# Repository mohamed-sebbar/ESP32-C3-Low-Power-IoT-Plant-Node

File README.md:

# ESP32-C3 Low-Power IoT Plant Node Rev 2.0

> Design and implementation of a compact low-power ESP32-C3 hardware platform for smart plant monitoring, environmental sensing and automated irrigation.

---

---

## Overview

This repository presents the complete hardware design of a compact ESP32-C3 based IoT plant monitoring node developed as an engineering-focused redesign of a previously demonstrated smart irrigation concept.

Where the original project validated the overall application concept, this work focuses on the complete hardware architecture, RF-aware PCB layout, mixed-signal design, manufacturability, power integrity, and long-term maintainability of a production-oriented embedded platform.

The platform integrates environmental sensing, wireless communication, battery-ready power management and irrigation control within a compact four-layer PCB specifically designed for constrained enclosure geometries.

The goal of this repository is to document the engineering process behind the hardware rather than only presenting a finished PCB.

---

## Contents

- [Overview](#overview)
- [Key Features](#key-features)
- [Hardware Gallery](#hardware-gallery)
- [Repository Structure](#repository-structure)
- [Hardware Architecture](#hardware-architecture)
- [PCB Design Highlights](#pcb-design-highlights)
- [RF Design](#rf-design)
- [Manufacturing](#manufacturing)
- [Documentation](#documentation)
- [Future Work](#future-work)
- [Acknowledgements](#acknowledgements)
- [License](#license)
- [Author](#author)
- [Contact](#contact)

---

## Key Features

- Custom 4-layer PCB
- ESP32-C3 Wi-Fi MCU
- External SPI Flash
- USB-C Programming & Power
- Battery-ready architecture
- Battery charging circuitry
- Reverse polarity protection
- SHT40 Temperature & Humidity Sensor
- Capacitive Soil Moisture Interface
- MOSFET-controlled irrigation pump
- 2.4 GHz PCB antenna based on TI reference design
- RF-aware PCB layout
- Mixed-signal architecture
- Ground stitching
- Manufacturing-ready design

---

## Hardware Gallery

---

## Repository Structure

```text
ESP32-C3-Low-Power-IoT-Plant-Node

├── Hardware/
│   ├── KiCad Project
│   ├── Production
│   └── Libraries
│
├── Docs/
│   ├── 01_Schematic.pdf
│   └── 02_PCB_Assembly.pdf
│
├── LTspice_Sim
│
├── Images/
│
├── Logos/
│
├── 3D Models/
│
├── LICENSE
└── README.md
```
### Quick Access

- 📁 [Hardware](Hardware/)
- 📁 [Docs](Docs/)
- 📁 [LTspice_Sim](LTspice_Sim/)
- 📁 [Images](Images/)
- 📁 [Logos](Logos/)
- 📁 [3D Models](3D%20Models/)

---

## Hardware Architecture

The platform combines multiple engineering domains within a compact embedded hardware design.

**Processing**

- ESP32-C3
- External SPI Flash

**Environmental Sensing**

- SHT40 Temperature & Humidity
- Capacitive Soil Moisture Sensor

**Irrigation**

- MOSFET Pump Driver
- External Pump Connector

**Connectivity**

- Wi-Fi
- USB-C

**Power**

- USB & Battery powered
- Battery charging supported
- Reverse polarity protection
- Battery voltage monitoring

---

## PCB Design Highlights

The PCB was designed from the ground up with emphasis on engineering practices commonly employed in professional embedded hardware development.

Highlights include

- Four-layer stack-up
- Continuous ground reference planes
- Controlled RF keep-out
- Ground stitching vias
- Short crystal routing
- Careful decoupling placement
- USB differential routing
- Mixed analog/digital partitioning
- Compact constrained mechanical form factor

---

## RF Design

The wireless subsystem employs a PCB antenna derived from Texas Instruments reference **AN043** recommendations.

The antenna region includes

- dedicated RF keep-out
- controlled ground clearance
- dedicated feed routing
- configurable matching network

The initial values of the antenna matching network (L2, C21, C22) were selected based on theoretical calculations and RF design recommendations. Although these values are expected to operate correctly, final impedance matching should be verified after fabrication. For this reason, it is recommended to initially designate L2, C21, and C22 as DNP (Do Not Populate) and populate them only after RF characterization and tuning of the assembled hardware.

Detailed RF design notes will be provided in future documentation.

---

## Manufacturing

The repository includes fabrication outputs required for PCB production.

Included

- Gerber files
- Drill files
- Fabrication outputs

A generic Bill of Materials (BOM) is provided for design reference. Manufacturer-specific part numbers and sourcing information are intentionally omitted, allowing designers the flexibility to select equivalent components based on availability, cost, or project-specific requirements.

---

## Documentation

The repository documentation is being expanded and currently includes

- Schematic
- PCB Assembly
- LTspice power rail stability and transient response plots

Planned additions

- PCB Design Report
- RF Design Notes
- Signal and Power Integrity Discussion
- Design Validation

---

## Future Work

- Firmware adaptation
- Antenna impedance tuning
- Battery validation [Done]
- Power consumption characterization [Done]
- Environmental testing
- Long-term field deployment
- Companion mobile application integration

---

## Acknowledgements

The 3D planter model used in the project renders was created by **Lewis**. Full credit goes to the original author. The original model is available on the **Thingiverse** [Profile](https://www.thingiverse.com/thing:3537287).

The plant icon used on the PCB silkscreen is **"Smart Plant"** by **Anton Handal Saputra**, sourced from the **Noun Project**, and is used under the **Creative Commons Attribution 3.0 (CC BY 3.0)** license: https://thenounproject.com/browse/icons/term/smart-plant/

---

## License

The hardware design files are released under the CERN Open Hardware Licence Version 2 – Permissive (CERN-OHL-P). The accompanying files and written documentation remain © 2026 SEBBAR Mohamed and are provided for reference purposes only.

See [LICENSE](LICENSE) for details.

---

## Author

**Mohamed Sebbar**

Master's Degree in Computer Engineering and Embedded Systems

Faculty of Sciences, Agadir, Morocco

---

## Contact

If you have questions about this project, or would like to discuss the design feel free to:

- Open an [Issue](../../issues).
- Connect with me on [LinkedIn](https://www.linkedin.com/in/mohamedsebbar/).
- Or contact me via [email](mailto:sebbar.mohamed66@gmail.com).

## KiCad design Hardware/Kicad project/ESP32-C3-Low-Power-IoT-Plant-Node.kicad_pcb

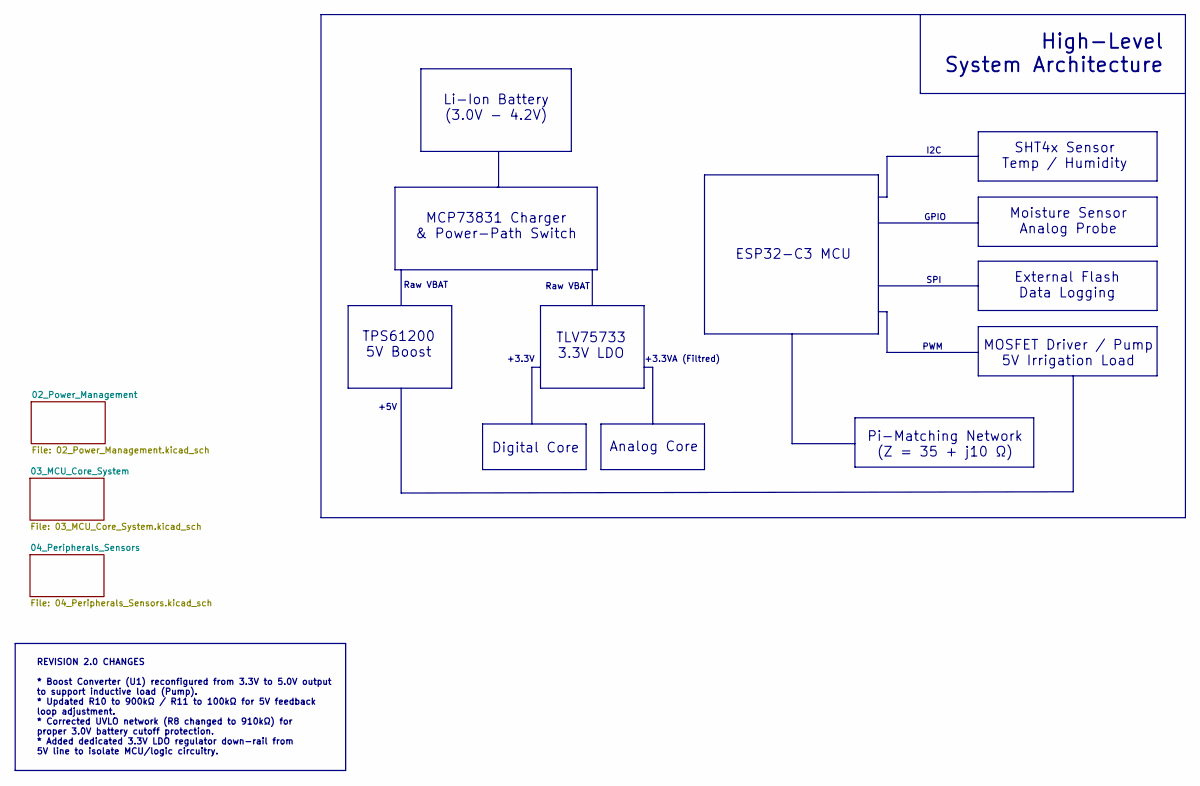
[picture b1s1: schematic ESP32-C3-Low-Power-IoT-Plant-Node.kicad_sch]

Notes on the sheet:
Moisture Sensor Analog Probe
Analog Core
ESP32-C3 MCU
Raw VBAT
+3.3VA (Filtred)
I2C
+5V
GPIO
Pi-Matching Network (Z = 35 + j10 Ω)
High-Level System Architecture
TLV75733 3.3V LDO
SPI
Digital Core
TPS61200 5V Boost
MOSFET Driver / Pump 5V Irrigation Load
REVISION 2.0 CHANGES * Boost Converter (U1) reconfigured from 3.3V to 5.0V output to support inductive load (Pump). * Updated R10 to 900kΩ / R11 to 100kΩ for 5V feedback loop adjustment. * Corrected UVLO network (R8 changed to 910kΩ) for proper 3.0V battery cutoff protection. * Added dedicated 3.3V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
SHT4x Sensor Temp / Humidity
PWM
MCP73831 Charger & Power-Path Switch
+3.3V
Li-Ion Battery (3.0V - 4.2V)
External Flash Data Logging

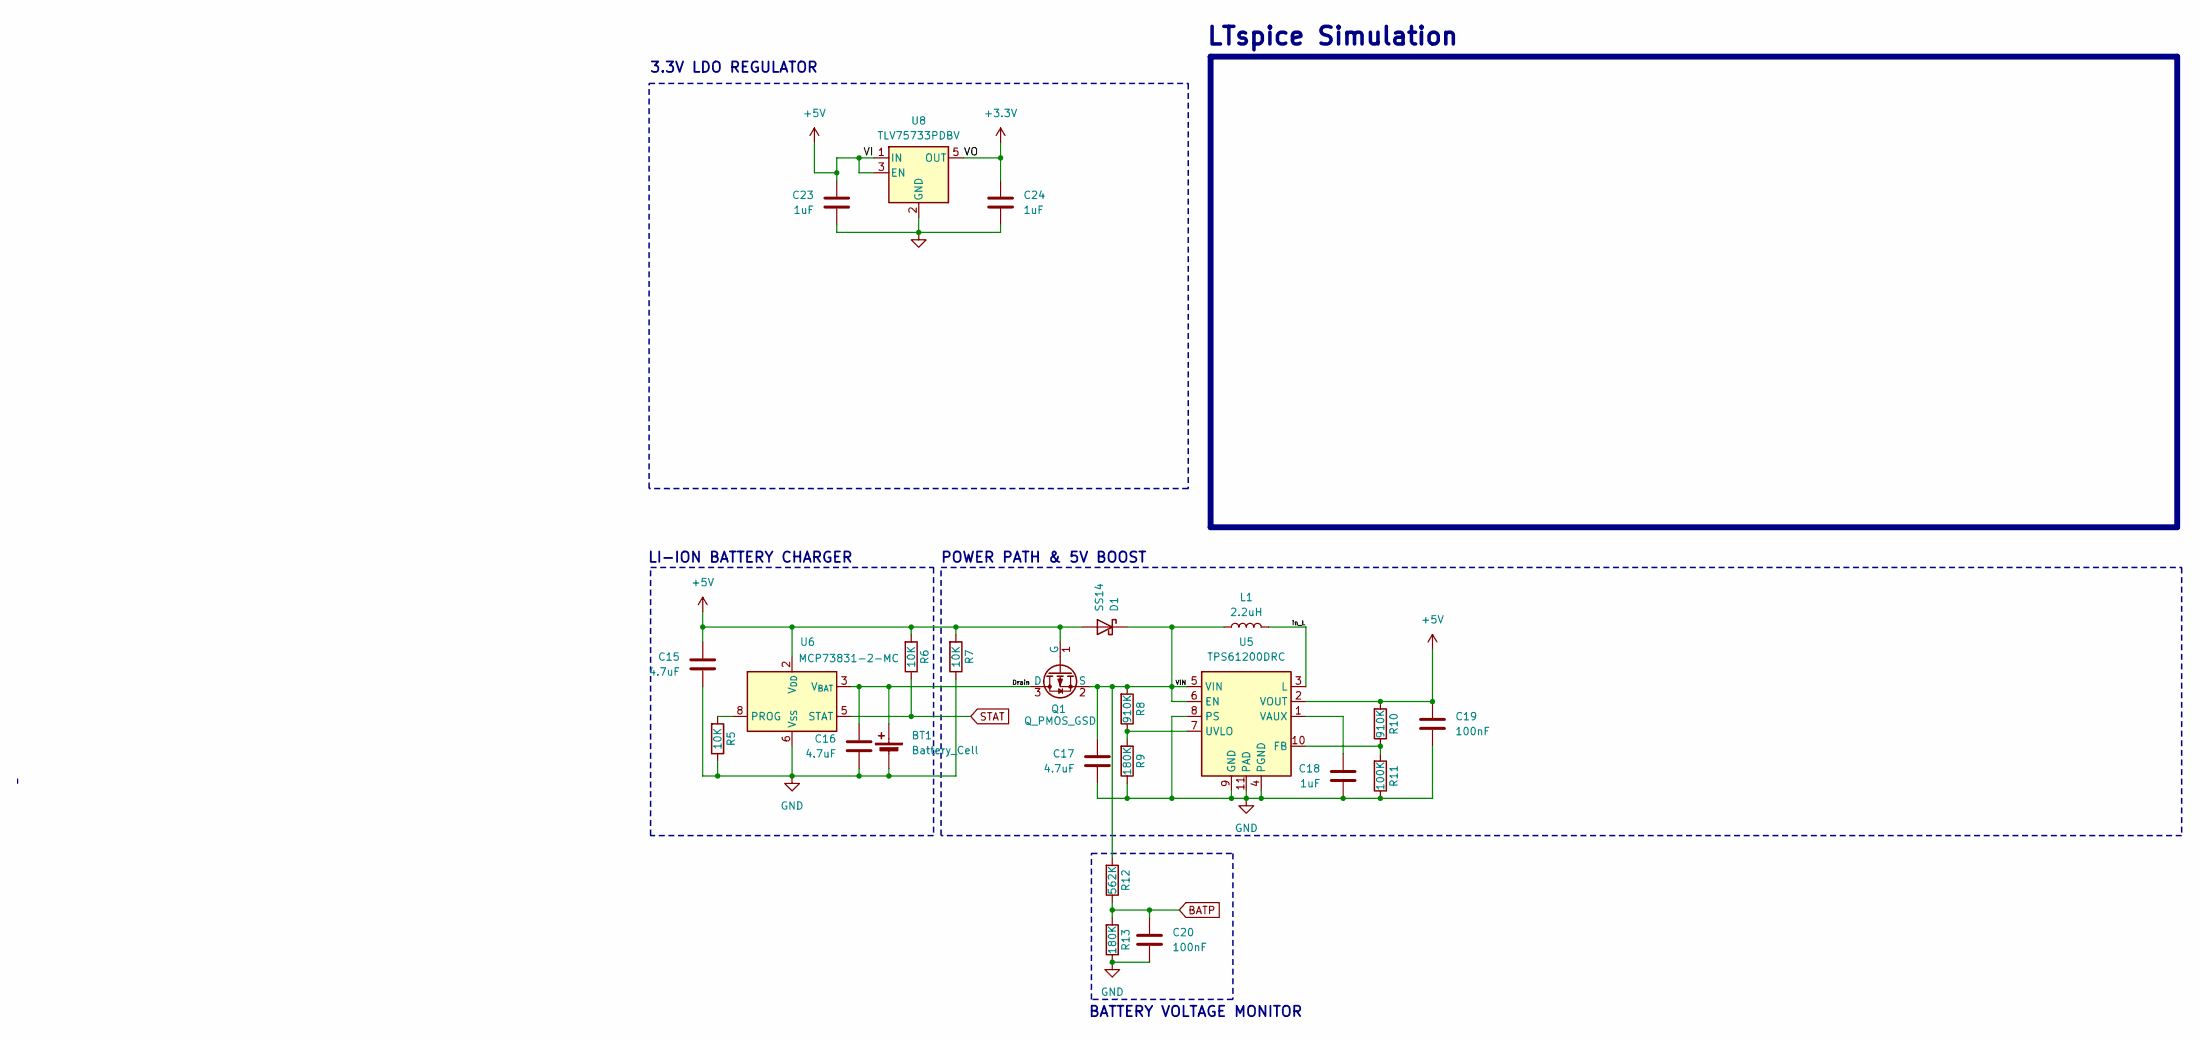
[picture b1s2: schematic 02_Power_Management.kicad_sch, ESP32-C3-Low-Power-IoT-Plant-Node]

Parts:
BT1: Battery_Cell; JST_PH_S2B-PH-K_1x02_P2.00mm_Horizontal
C15, C16, C17: 4.7uF; C_0402_1005Metric
C18, C23, C24: 1uF; C_0402_1005Metric
C19, C20: 100nF; C_0402_1005Metric
D1: SS14; D_SMA
L1: 2.2uH; R_0402_1005Metric
Q1: Q_PMOS_GSD; SOT-23
R5, R6, R7: 10K; R_0402_1005Metric
R8, R10: 910K; R_0402_1005Metric
R9, R13: 180K; R_0402_1005Metric
R11: 100K; R_0402_1005Metric
R12: 562K; R_0402_1005Metric
U5: TPS61200DRC; Texas_S-PVSON-N10_ThermalVias
U6: MCP73831-2-MC; DFN-8-1EP_3x2mm_P0.5mm_EP1.75x1.45mm
U8: TLV75733PDBV; SOT-23-5

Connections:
+3.3V: C24.1, U8.5 (OUT); also elsewhere on the board
+5V: C15.1, C19.1, C23.1, D1.2 (A), Q1.1 (G), R6.2, R7.2, R10.2, U5.2 (VOUT), U6.1 (V_{DD}), U6.2 (V_{DD}), U8.1 (IN), U8.3 (EN); also elsewhere on the board
/02_Power_Management/Drain: BT1.1 (+), C16.1, Q1.3 (D), U6.3 (V_{BAT}), U6.4 (V_{BAT})
/02_Power_Management/VIN: C17.1, D1.1 (K), L1.1, Q1.2 (S), R8.2, R12.2, U5.5 (VIN), U5.6 (EN)
/02_Power_Management/in_L: L1.2, U5.3 (L)
BATP: C20.1, R12.1, R13.2; also elsewhere on the board
GND: BT1.2 (-), C15.2, C16.2, C17.2, C18.2, C19.2, C20.2, C23.2, C24.2, R5.1, R7.1, R9.1, R11.1, R13.1, U5.4 (PGND), U5.8 (PS), U5.9 (GND), U5.11 (PAD), U6.6 (V_{SS}), U8.2 (GND); also elsewhere on the board
unnamed: R10.1, R11.2, U5.10 (FB)
unnamed: R8.1, R9.2, U5.7 (UVLO)
unnamed: C18.1, U5.1 (VAUX)
unnamed: R5.2, U6.8 (PROG)
STAT: R6.1, U6.5 (STAT); also elsewhere on the board

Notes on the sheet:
BATTERY VOLTAGE MONITOR
POWER PATH & 5V BOOST
3.3V LDO REGULATOR
LTspice Simulation
LI-ION BATTERY CHARGER

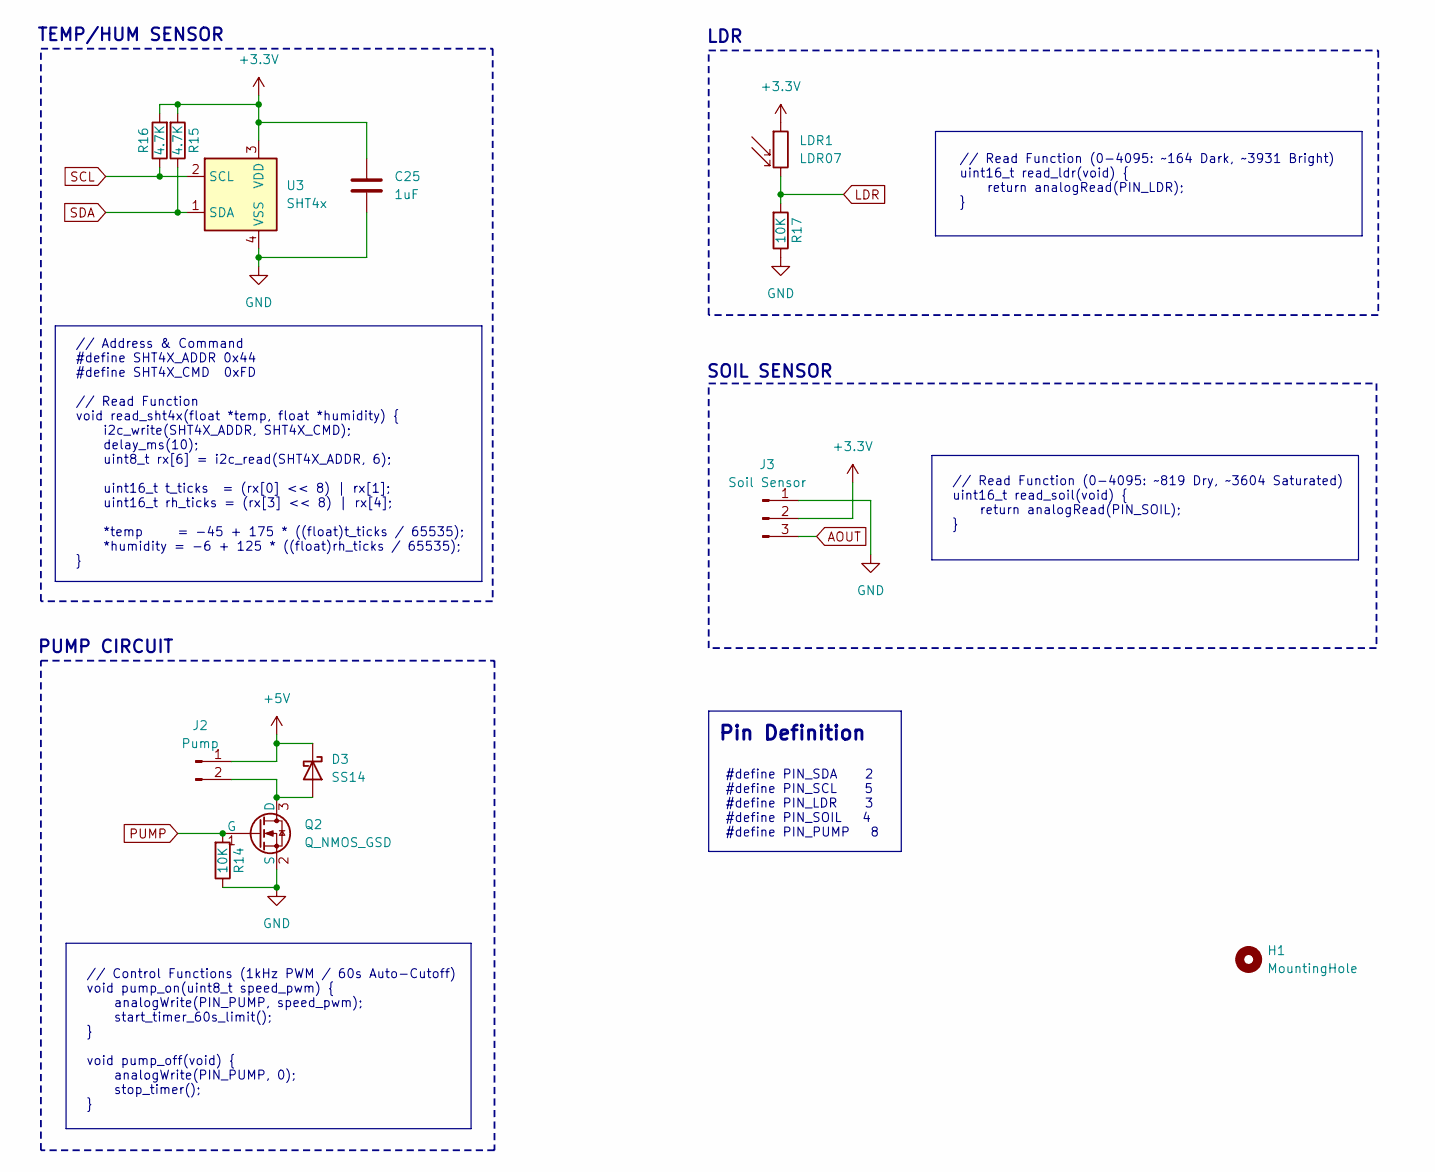
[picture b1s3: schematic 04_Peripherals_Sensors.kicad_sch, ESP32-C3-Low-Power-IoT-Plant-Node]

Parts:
C25: 1uF; C_0402_1005Metric
D3: SS14; D_SMA
H1: MountingHole; MountingHole_2.1mm
J2: Pump; JST_PH_B2B-PH-K_1x02_P2.00mm_Vertical
J3: Soil Sensor; JST_PH_B3B-PH-K_1x03_P2.00mm_Vertical
LDR1: LDR07; R_LDR_5.1x4.3mm_P3.4mm_Vertical
Q2: Q_NMOS_GSD; SOT-23
R14, R17: 10K; R_0402_1005Metric
R15, R16: 4.7K; R_0402_1005Metric
U3: SHT4x; Sensirion_DFN-4_1.5x1.5mm_P0.8mm_SHT4x_NoCentralPad

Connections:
+3.3V: C25.1, J3.2, LDR1.1, R15.2, R16.2, U3.3 (VDD); also elsewhere on the board
+5V: D3.1 (K), J2.1; also elsewhere on the board
AOUT: J3.3; also elsewhere on the board
GND: C25.2, J3.1, Q2.2 (S), R14.1, R17.1, U3.4 (VSS); also elsewhere on the board
LDR: LDR1.2, R17.2; also elsewhere on the board
unnamed: D3.2 (A), J2.2, Q2.3 (D)
PUMP: Q2.1 (G), R14.2; also elsewhere on the board
SCL: R16.1, U3.2 (SCL); also elsewhere on the board
SDA: R15.1, U3.1 (SDA); also elsewhere on the board

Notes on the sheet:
// Read Function (0-4095: ~164 Dark, ~3931 Bright) uint16_t read_ldr(void) { return analogRead(PIN_LDR); }
// Address & Command #define SHT4X_ADDR 0x44 #define SHT4X_CMD 0xFD // Read Function void read_sht4x(float *temp, float *humidity) { i2c_write(SHT4X_ADDR, SHT4X_CMD); delay_ms(10); uint8_t rx[6] = i2c_read(SHT4X_ADDR, 6); uint16_t t_ticks = (rx[0] << 8) | rx[1]; uint16_t rh_ticks = (rx[3] << 8) | r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
PUMP CIRCUIT
LDR
TEMP/HUM SENSOR
// Read Function (0-4095: ~819 Dry, ~3604 Saturated) uint16_t read_soil(void) { return analogRead(PIN_SOIL); }
// Control Functions (1kHz PWM / 60s Auto-Cutoff) void pump_on(uint8_t speed_pwm) { analogWrite(PIN_PUMP, speed_pwm); start_timer_60s_limit(); } void pump_off(void) { analogWrite(PIN_PUMP, 0); stop_timer(); }
#define PIN_SDA 2 #define PIN_SCL 5 #define PIN_LDR 3 #define PIN_SOIL 4 #define PIN_PUMP 8
Pin Definition
SOIL SENSOR

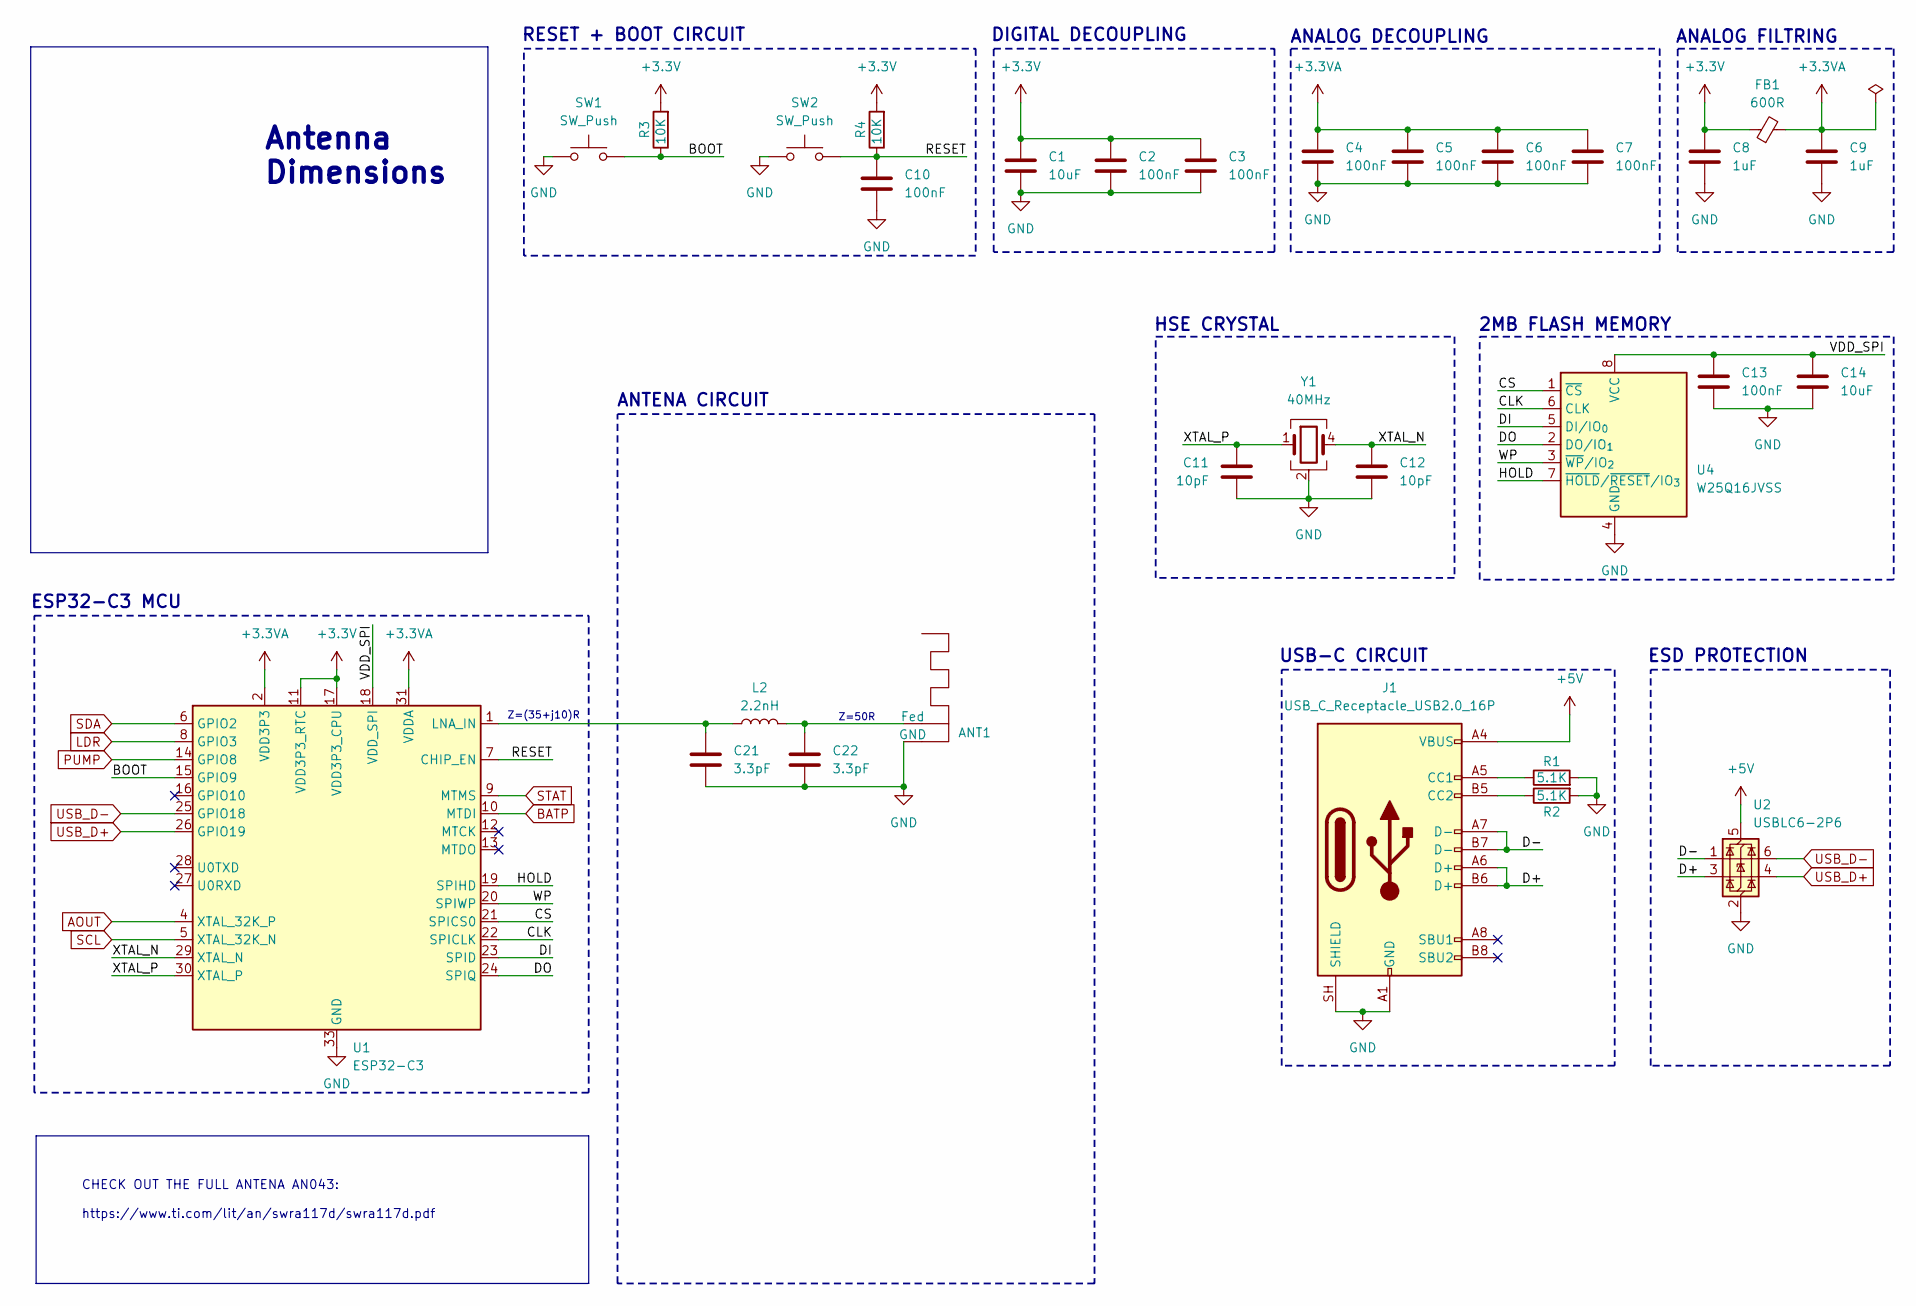
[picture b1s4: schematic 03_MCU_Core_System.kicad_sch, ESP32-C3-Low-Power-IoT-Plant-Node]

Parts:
ANT1: RF_TI_Antena_2.4GHz_flipped
C1, C14: 10uF; C_0402_1005Metric
C2, C3, C4, C5, C6, C7, C10, C13: 100nF; C_0402_1005Metric
C8, C9: 1uF; C_0402_1005Metric
C11, C12: 10pF; C_0402_1005Metric
C21, C22: 3.3pF; C_0402_1005Metric
FB1: 600R; R_0402_1005Metric
J1: USB_C_Receptacle_USB2.0_16P; USB_C_Receptacle_GCT_USB4105-xx-A_16P_TopMnt_Horizontal
L2: 2.2nH; R_0402_1005Metric
R1, R2: 5.1K; R_0402_1005Metric
R3, R4: 10K; R_0402_1005Metric
SW1, SW2: SW_Push; SW_Push_SPST_NO_Alps_SKRK
U1: ESP32-C3; QFN-32-1EP_5x5mm_P0.5mm_EP3.7x3.7mm
U2: USBLC6-2P6; SOT-666
U4: W25Q16JVSS; SOIC-8_5.3x5.3mm_P1.27mm
Y1: 40MHz; Crystal_SMD_3225-4Pin_3.2x2.5mm

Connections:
+3.3V: C1.1, C2.1, C3.1, C8.1, FB1.1, R3.2, R4.2, U1.11 (VDD3P3_RTC), U1.17 (VDD3P3_CPU); also elsewhere on the board
+3.3VA: C4.1, C5.1, C6.1, C7.1, C9.1, FB1.2, U1.2 (VDD3P3), U1.3 (VDD3P3), U1.31 (VDDA), U1.32 (VDDA)
+5V: J1.A4 (VBUS), J1.A9 (VBUS), J1.B4 (VBUS), J1.B9 (VBUS), U2.5 (VBUS); also elsewhere on the board
/03_MCU_Core_System/BOOT: R3.1, SW1.2, U1.15 (GPIO9)
/03_MCU_Core_System/CLK: U1.22 (SPICLK), U4.6 (CLK)
/03_MCU_Core_System/CS: U1.21 (SPICS0), U4.1 (~CS)
/03_MCU_Core_System/D+: J1.A6 (D+), J1.B6 (D+), U2.3 (I/O2)
/03_MCU_Core_System/D-: J1.A7 (D-), J1.B7 (D-), U2.1 (I/O1)
/03_MCU_Core_System/DI: U1.23 (SPID), U4.5 (DI/IO_{0})
/03_MCU_Core_System/DO: U1.24 (SPIQ), U4.2 (DO/IO_{1})
/03_MCU_Core_System/HOLD: U1.19 (SPIHD), U4.7 (~HOLD/~RESET/IO_{3})
/03_MCU_Core_System/RESET: C10.1, R4.1, SW2.2, U1.7 (CHIP_EN)
/03_MCU_Core_System/VDD_SPI: C13.1, C14.1, U1.18 (VDD_SPI), U4.8 (VCC)
/03_MCU_Core_System/WP: U1.20 (SPIWP), U4.3 (~WP/IO_{2})
/03_MCU_Core_System/XTAL_N: C12.1, U1.29 (XTAL_N), Y1.4
/03_MCU_Core_System/XTAL_P: C11.1, U1.30 (XTAL_P), Y1.1
AOUT: U1.4 (XTAL_32K_P); also elsewhere on the board
BATP: U1.10 (MTDI); also elsewhere on the board
GND: ANT1.2 (GND), C1.2, C2.2, C3.2, C4.2, C5.2, C6.2, C7.2, C8.2, C9.2, C10.2, C11.2, C12.2, C13.2, C14.2, C21.2, C22.2, J1.A1 (GND), J1.A12 (GND), J1.B1 (GND), J1.B12 (GND), J1.SH (SHIELD), R1.2, R2.2, SW1.1, SW2.1, U1.33 (GND), U2.2 (GND), U4.4 (GND), Y1.2 (G), Y1.3 (G); also elsewhere on the board
LDR: U1.8 (GPIO3); also elsewhere on the board
unnamed: ANT1.1 (Fed), C22.1, L2.2
unnamed: J1.A5 (CC1), R1.1
unnamed: J1.B5 (CC2), R2.1
unnamed: C21.1, L2.1, U1.1 (LNA_IN)
PUMP: U1.14 (GPIO8); also elsewhere on the board
SCL: U1.5 (XTAL_32K_N); also elsewhere on the board
SDA: U1.6 (GPIO2); also elsewhere on the board
STAT: U1.9 (MTMS); also elsewhere on the board
USB_D+: U1.26 (GPIO19), U2.4 (I/O2)
USB_D-: U1.25 (GPIO18), U2.6 (I/O1)

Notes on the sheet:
ANALOG FILTRING
ESD PROTECTION
2MB FLASH MEMORY
CHECK OUT THE FULL ANTENA AN043: https://www.ti.com/lit/an/swra117d/swra117d.pdf
HSE CRYSTAL
USB-C CIRCUIT
Z=(35+j10)R
ANALOG DECOUPLING
Antenna Dimensions
RESET + BOOT CIRCUIT
ANTENA CIRCUIT
Z=50R
ESP32-C3 MCU
DIGITAL DECOUPLING

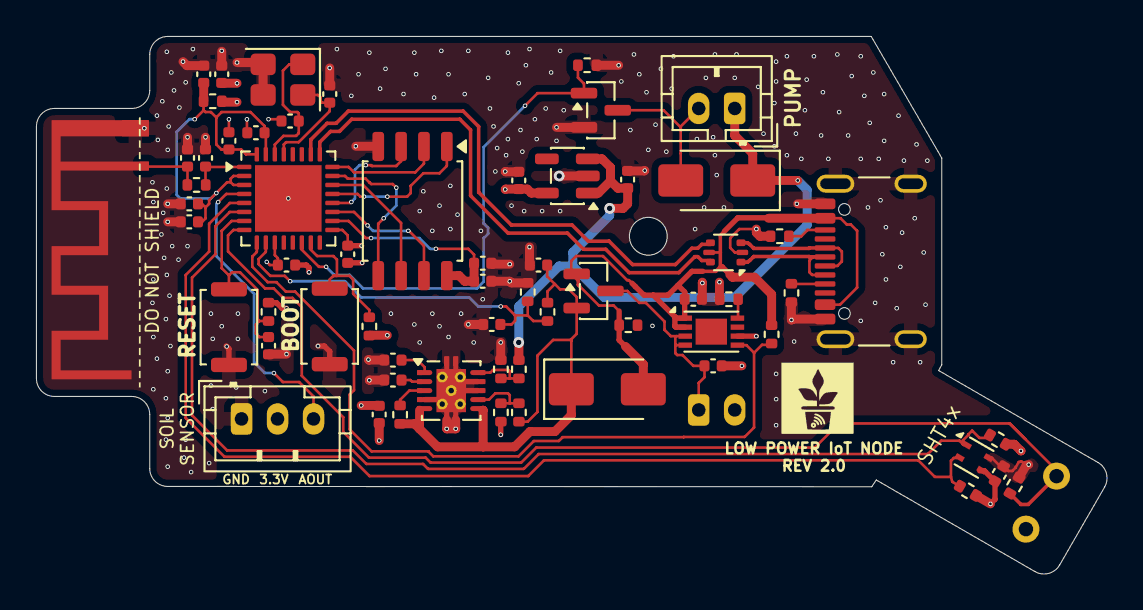
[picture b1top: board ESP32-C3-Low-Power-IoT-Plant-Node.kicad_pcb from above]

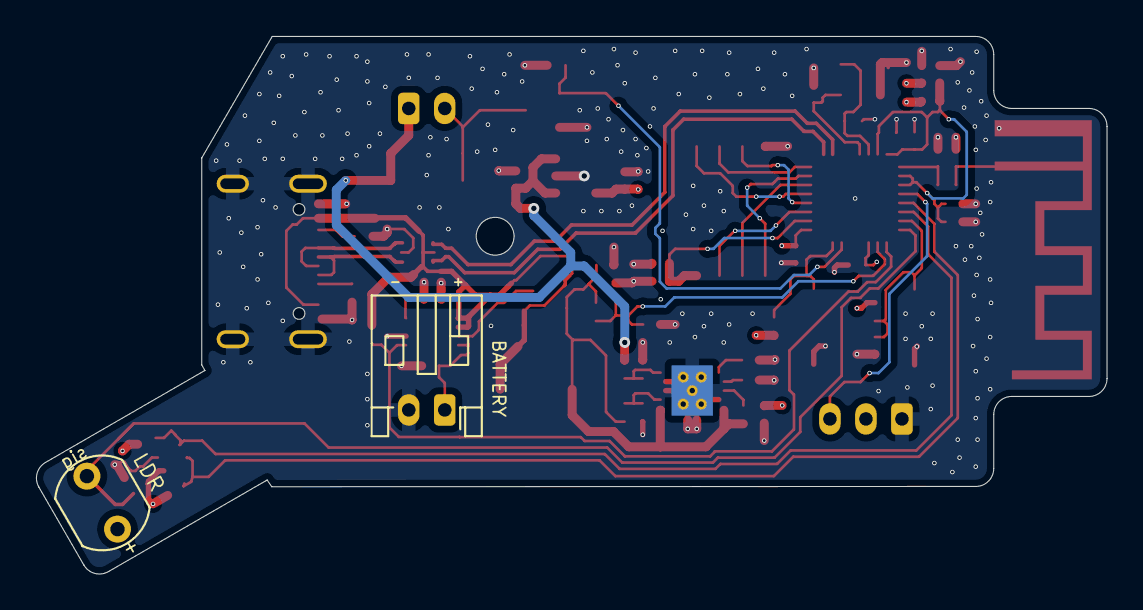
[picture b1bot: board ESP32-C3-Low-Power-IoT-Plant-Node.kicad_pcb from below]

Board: 4 copper layers, 59.5 x 29.9 mm, 66 parts (2 on the bottom side), 38 nets.

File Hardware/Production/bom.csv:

Designator,Footprint,Quantity,Value,LCSC Part #
ANT1,RF_TI_Antena_2.4GHz_flipped,1,~,
BT1,JST_PH_S2B-PH-K_1x02_P2.00mm_Horizontal,1,Battery_Cell,
"C1, C14",0402,2,10uF,
"C10, C13, C19, C2, C20, C3, C4, C5, C6, C7",0402,10,100nF,
"C11, C12",0402,2,10pF,
"C15, C16, C17",0402,3,4.7uF,
"C18, C23, C24, C25, C8, C9",0402,6,1uF,
"C21, C22",0402,2,3.3pF,
"D1, D3",D_SMA,2,SS14,
FB1,0402,1,600R,
J1,USB_C_Receptacle_GCT_USB4105-xx-A_16P_TopMnt_Horizontal,1,USB_C_Receptacle_USB2.0_16P,
J2,JST_PH_B2B-PH-K_1x02_P2.00mm_Vertical,1,Pump,
J3,JST_PH_B3B-PH-K_1x03_P2.00mm_Vertical,1,Soil Sensor,
L1,0402,1,2.2uH,
L2,0402,1,2.2nH,
LDR1,R_LDR_5.1x4.3mm_P3.4mm_Vertical,1,LDR07,
Q1,SOT-23,1,Q_PMOS_GSD,
Q2,SOT-23,1,Q_NMOS_GSD,
"R1, R2",0402,2,5.1K,
"R10, R8",0402,2,910K,
R11,0402,1,100K,
R12,0402,1,562K,
"R13, R9",0402,2,180K,
"R14, R17, R3, R4, R5, R6, R7",0402,7,10K,
"R15, R16",0402,2,4.7K,
"SW1, SW2",SW_Push_SPST_NO_Alps_SKRK,2,SW_Push,
U1,QFN-32-1EP_5x5mm_P0.5mm_EP3.7x3.7mm,1,ESP32-C3,
U2,SOT-666,1,USBLC6-2P6,
U3,Sensirion_DFN-4_1.5x1.5mm_P0.8mm_SHT4x_NoCentralPad,1,SHT4x,
U4,SOIC-8_5.3x5.3mm_P1.27mm,1,W25Q16JVSS,
U5,Texas_S-PVSON-N10_ThermalVias,1,TPS61200DRC,
U6,DFN-8-1EP_3x2mm_P0.5mm_EP1.75x1.45mm,1,MCP73831-2-MC,
U8,SOT-23-5,1,TLV75733PDBV,
Y1,Crystal_SMD_3225-4Pin_3.2x2.5mm,1,40MHz,
